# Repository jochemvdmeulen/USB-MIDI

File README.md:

# USB-MIDI
PCB Desgin for converter that converts USB MIDI to regular MIDI based on hobbytronics.co.uk USB Host IC and software

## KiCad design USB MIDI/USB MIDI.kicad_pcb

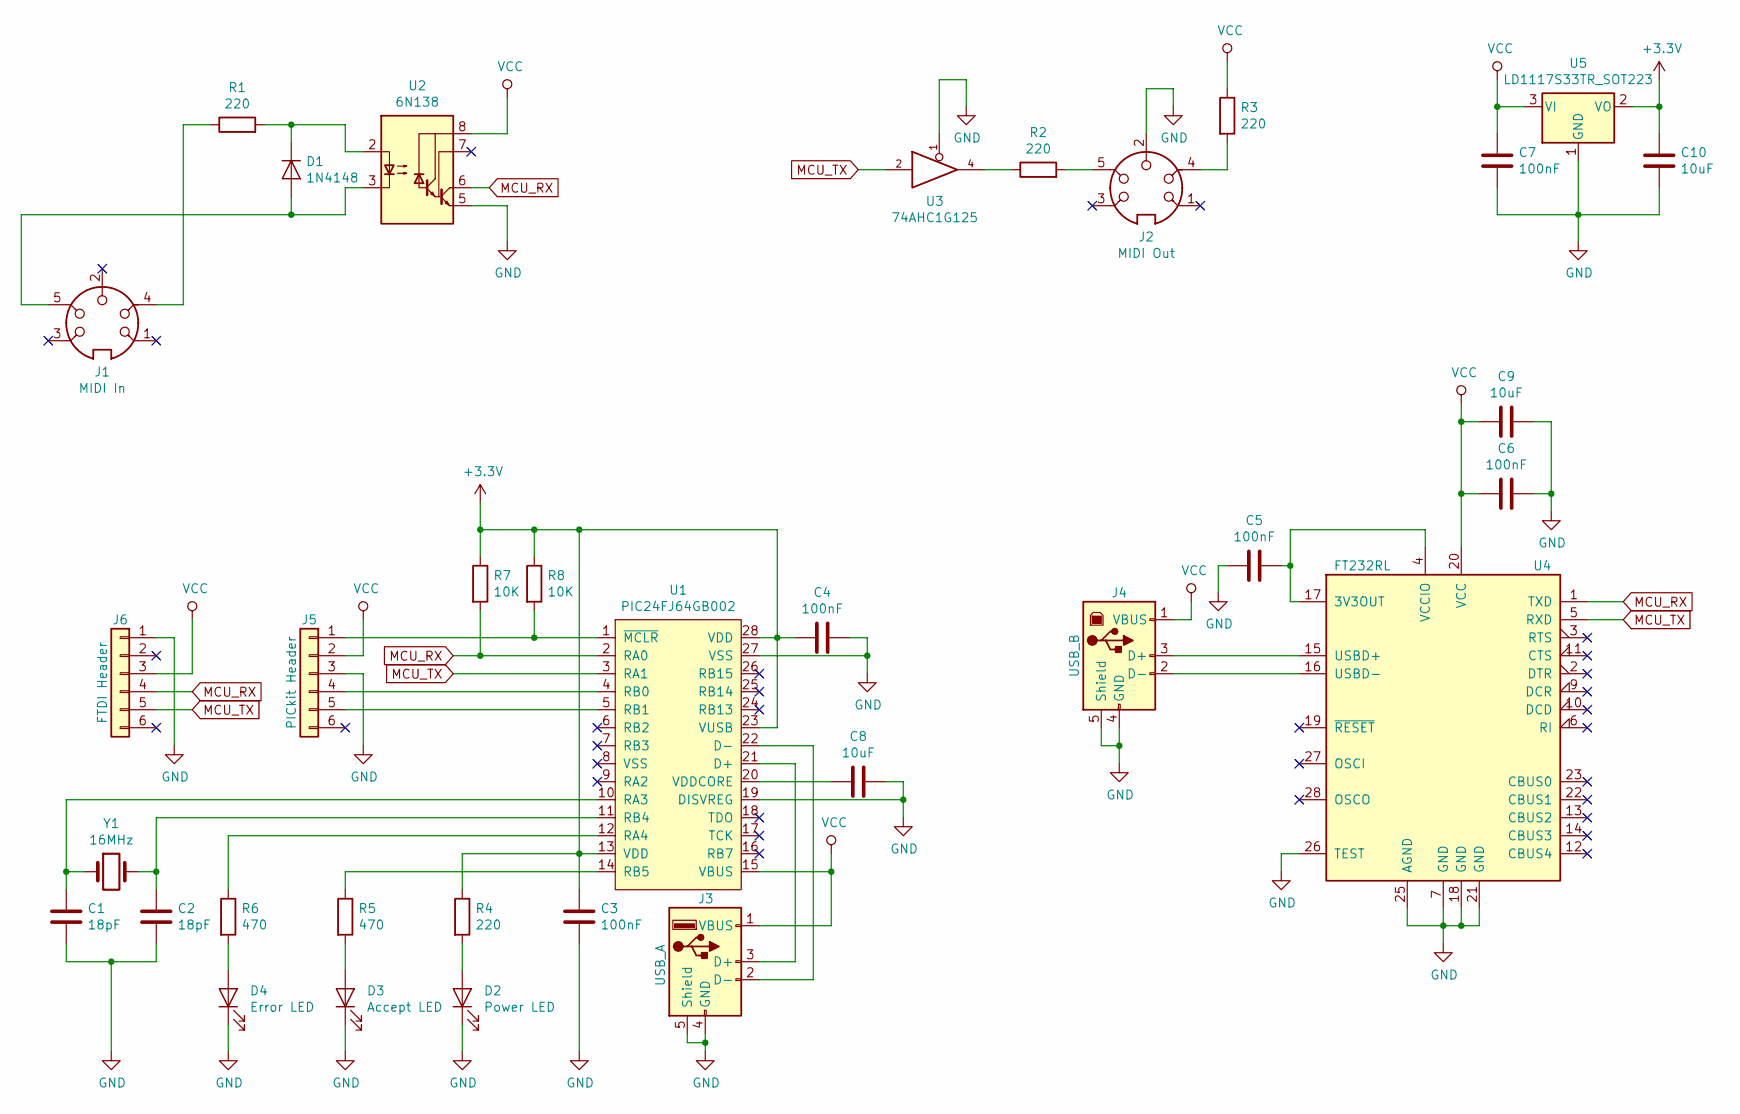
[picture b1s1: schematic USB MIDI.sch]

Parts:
C1, C2: 18pF; C_1206_3216Metric_Pad1.42x1.75mm_HandSolder
C3, C4, C5, C6, C7: 100nF; C_1206_3216Metric_Pad1.42x1.75mm_HandSolder
C8, C9, C10: 10uF; C_1206_3216Metric_Pad1.42x1.75mm_HandSolder
D1: 1N4148; D_SOD-123
D2: Power LED; LED_D3.0mm
D3: Accept LED; LED_D3.0mm
D4: Error LED; LED_D3.0mm
J1: MIDI In; din-5
J2: MIDI Out; din-5
J3: USB_A; FCI_87520-0010BLF
J4: USB_B; FCI_61729-1011BLF
J5: PICkit Header; PinHeader_1x06_P2.54mm_Vertical
J6: FTDI Header; PinHeader_1x06_P2.54mm_Vertical
R1, R2, R3, R4: 220; R_1206_3216Metric_Pad1.42x1.75mm_HandSolder
R5, R6: 470; R_1206_3216Metric_Pad1.42x1.75mm_HandSolder
R7, R8: 10K; R_1206_3216Metric_Pad1.42x1.75mm_HandSolder
U1: PIC24FJ64GB002; SSOP-28_5.3x10.2mm_P0.65mm
U2: 6N138; DIP-8_W7.62mm_Socket_LongPads
U3: 74AHC1G125; SOT-23-5_HandSoldering
U4: FT232RL; SSOP-28_5.3x10.2mm_P0.65mm
U5: LD1117S33TR_SOT223; SOT-223-3_TabPin2
Y1: 16MHz; Crystal_HC49-4H_Vertical

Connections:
+3V3: C3.1, C4.2, C10.1, R4.1, R7.1, R8.1, U1.13 (VDD), U1.23 (VUSB), U1.28 (VDD), U5.2 (VO)
GND: C1.2, C2.2, C3.2, C4.1, C5.2, C6.1, C7.2, C8.1, C9.1, C10.2, D2.1 (K), D3.1 (K), D4.1 (K), J2.2, J2.6 (GND), J3.4 (GND), J3.5 (Shield), J3.P1, J3.P2, J4.4 (GND), J4.5 (Shield), J4.M1, J4.M2, J5.3, J6.1, U1.19 (DISVREG), U1.27 (VSS), U2.5 (GND), U3.1, U3.3 (GND), U4.7 (GND), U4.18 (GND), U4.21 (GND), U4.25 (AGND), U4.26 (TEST), U5.1 (GND)
MCU_RX: J6.4, R7.2, U1.2 (RA0), U2.6 (VO2), U4.1 (TXD)
MCU_TX: J6.5, U1.3 (RA1), U3.2, U4.5 (RXD)
unnamed: C1.1, U1.10 (RA3), Y1.1
unnamed: C2.1, U1.11 (RB4), Y1.2
unnamed: C5.1, U4.4 (VCCIO), U4.17 (3V3OUT)
unnamed: C8.2, U1.20 (VDDCORE)
unnamed: D1.1 (K), R1.2, U2.2 (C1)
unnamed: D1.2 (A), J1.5, U2.3 (C2)
unnamed: D2.2 (A), R4.2
unnamed: D3.2 (A), R5.2
unnamed: D4.2 (A), R6.2
unnamed: J1.4, R1.1
unnamed: J2.4, R3.2
unnamed: J2.5, R2.2
unnamed: J3.2 (D-), U1.22 (D-)
unnamed: J3.3 (D+), U1.21 (D+)
unnamed: J4.2 (D-), U4.16 (USBD-)
unnamed: J4.3 (D+), U4.15 (USBD+)
unnamed: J5.1, R8.2, U1.1 (~MCLR~)
unnamed: J5.4, U1.4 (RB0)
unnamed: J5.5, U1.5 (RB1)
unnamed: R2.1, U3.4
unnamed: R5.1, U1.14 (RB5)
unnamed: R6.1, U1.12 (RA4)
VCC: C6.2, C7.1, C9.2, J3.1 (VBUS), J4.1 (VBUS), J5.2, J6.3, R3.1, U1.15 (VBUS), U2.8 (VCC), U3.5 (VCC), U4.20 (VCC), U5.3 (VI)

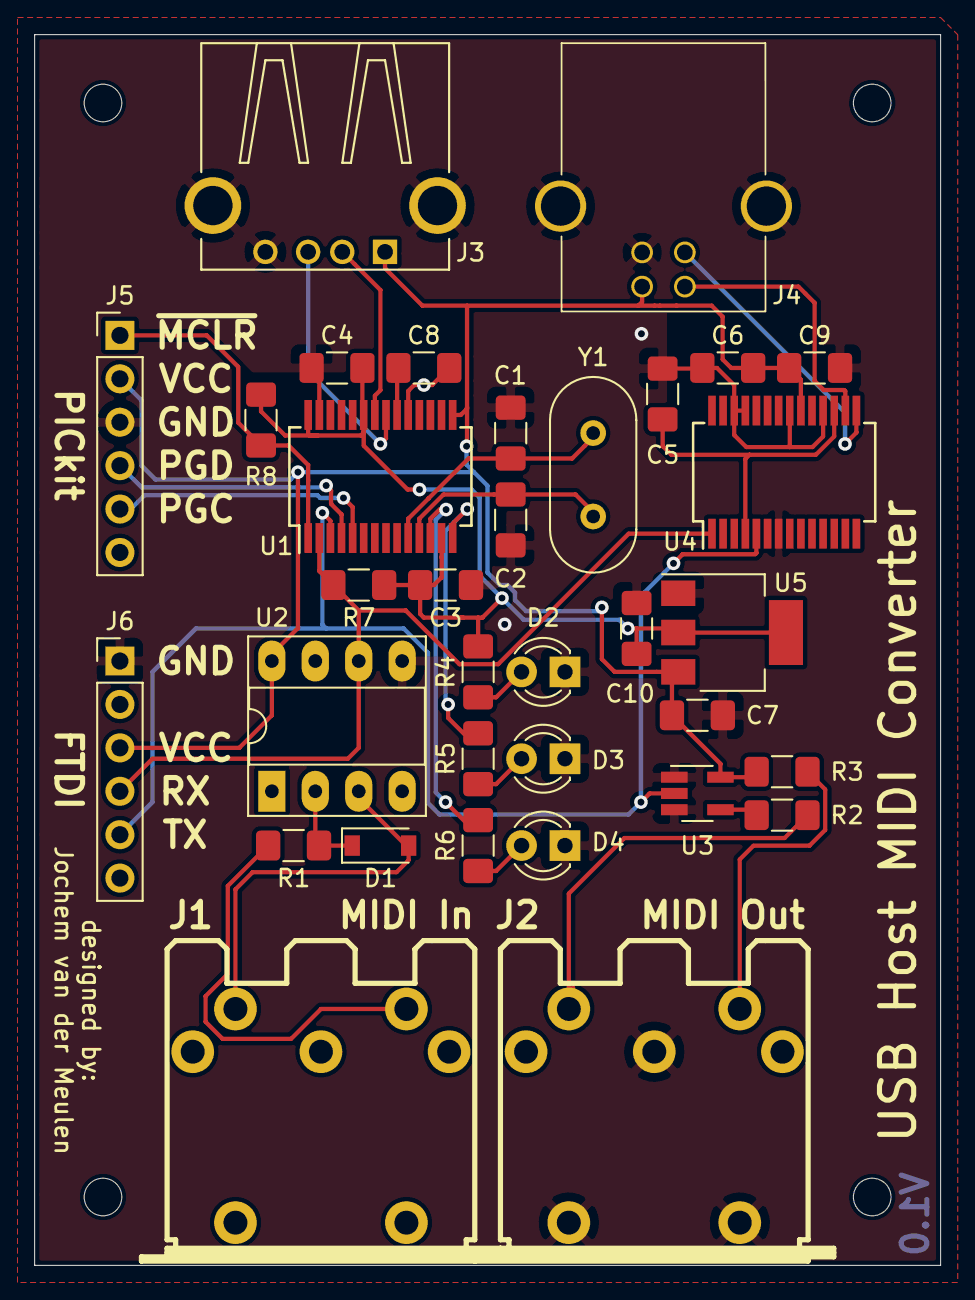
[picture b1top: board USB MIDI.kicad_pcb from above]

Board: 2 copper layers, 53.0 x 72.0 mm, 34 parts (0 on the bottom side), 27 nets.
